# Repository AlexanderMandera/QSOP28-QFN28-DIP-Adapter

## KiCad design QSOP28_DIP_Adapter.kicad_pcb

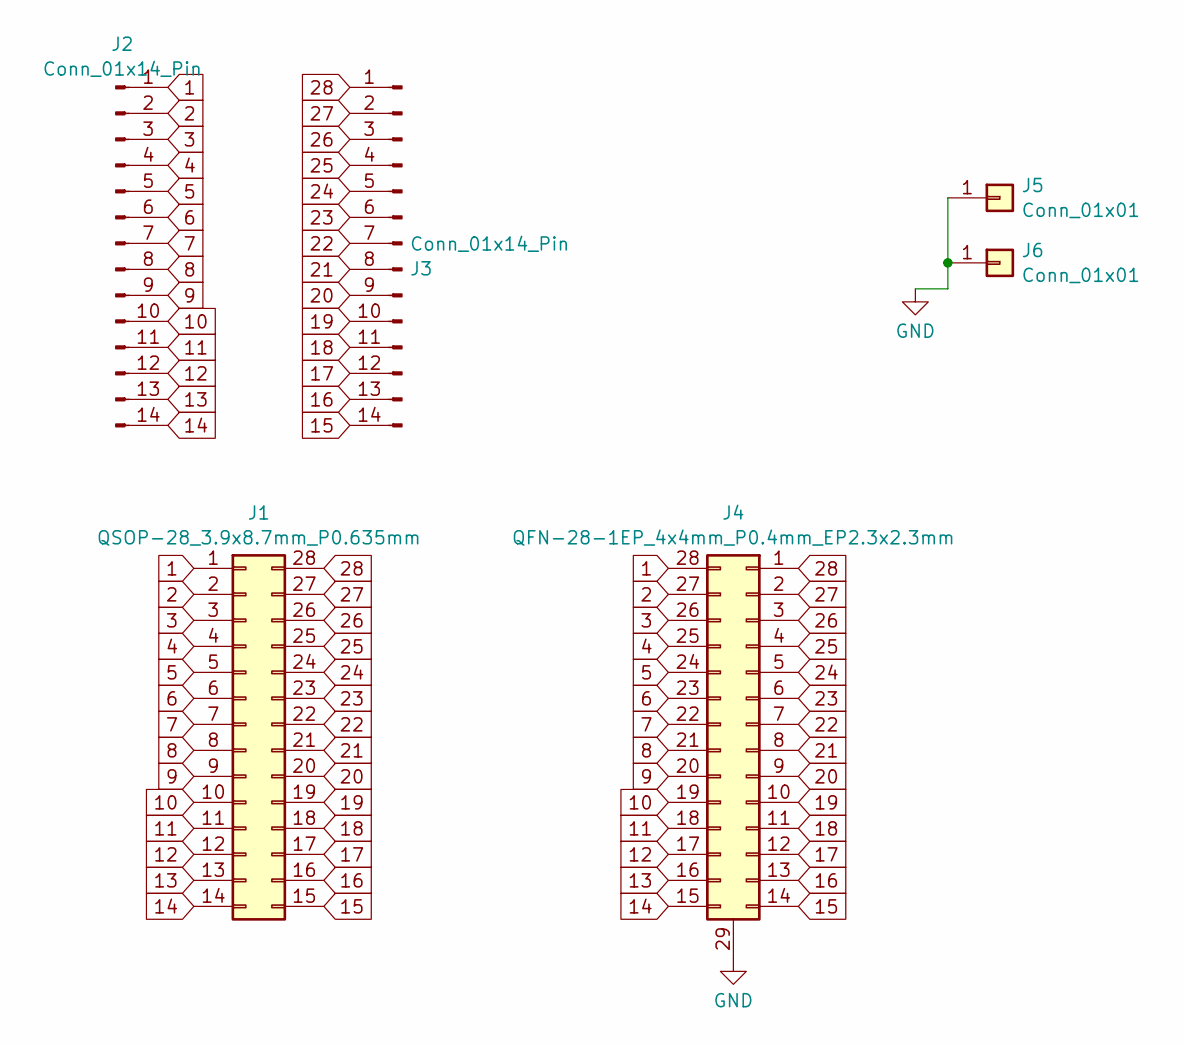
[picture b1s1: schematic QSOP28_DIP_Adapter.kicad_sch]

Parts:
J1: QSOP-28_3.9x8.7mm_P0.635mm
J2, J3: Conn_01x14_Pin; PinHeader_1x14_P2.54mm_Vertical
J4: QFN-28-1EP_4x4mm_P0.4mm_EP2.3x2.3mm
J5, J6: Conn_01x01; PinSocket_1x01_P2.54mm_Vertical

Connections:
1: J1.1, J2.1, J4.28
2: J1.2, J2.2, J4.27
3: J1.3, J2.3, J4.26
4: J1.4, J2.4, J4.25
5: J1.5, J2.5, J4.24
6: J1.6, J2.6, J4.23
7: J1.7, J2.7, J4.22
8: J1.8, J2.8, J4.21
9: J1.9, J2.9, J4.20
10: J1.10, J2.10, J4.19
11: J1.11, J2.11, J4.18
12: J1.12, J2.12, J4.17
13: J1.13, J2.13, J4.16
14: J1.14, J2.14, J4.15
15: J1.15, J3.14, J4.14
16: J1.16, J3.13, J4.13
17: J1.17, J3.12, J4.12
18: J1.18, J3.11, J4.11
19: J1.19, J3.10, J4.10
20: J1.20, J3.9, J4.9
21: J1.21, J3.8, J4.8
22: J1.22, J3.7, J4.7
23: J1.23, J3.6, J4.6
24: J1.24, J3.5, J4.5
25: J1.25, J3.4, J4.4
26: J1.26, J3.3, J4.3
27: J1.27, J3.2, J4.2
28: J1.28, J3.1, J4.1
GND: J4.29 (GND), J5.1, J6.1

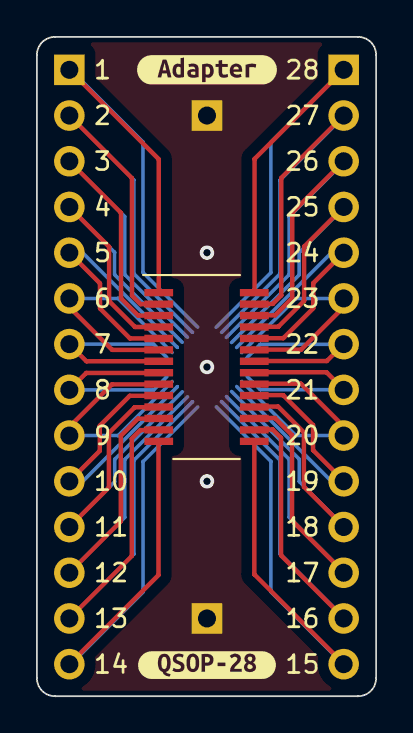
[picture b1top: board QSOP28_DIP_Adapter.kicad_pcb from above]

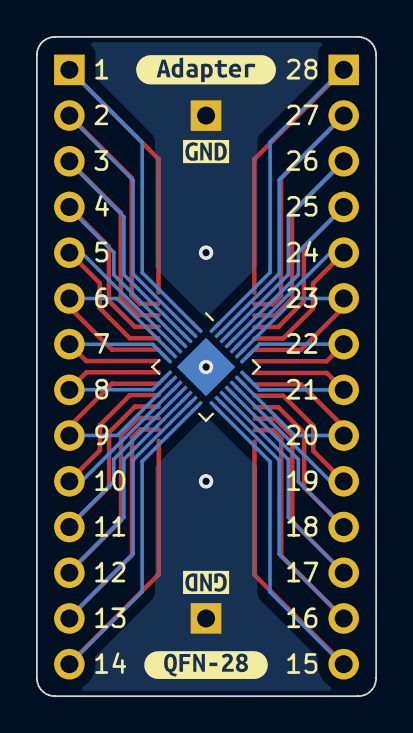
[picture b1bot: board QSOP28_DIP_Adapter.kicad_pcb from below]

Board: 2 copper layers, 18.8 x 36.6 mm, 12 parts (7 on the bottom side), 29 nets.

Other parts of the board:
kibuzzard-653FE0F3: G***; kibuzzard-653FE0F3
kibuzzard-653FE121: G***; kibuzzard-653FE121
kibuzzard-653FE141, kibuzzard-653FE141#2: G***; kibuzzard-653FE141
kibuzzard-6550E669, kibuzzard-6550E669#2: G***; kibuzzard-6550E669

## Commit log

2023-11-16 Add LICENSE
